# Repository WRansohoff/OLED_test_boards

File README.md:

# Overview

These are KiCAD projects with schematics and footprints for 128x64 SSD1306 monochrome OLED screens and 96x64 SSD1331 multicolor ones. Both panels are roughly 1" diagonally, and the boards are designed for SPI communication.

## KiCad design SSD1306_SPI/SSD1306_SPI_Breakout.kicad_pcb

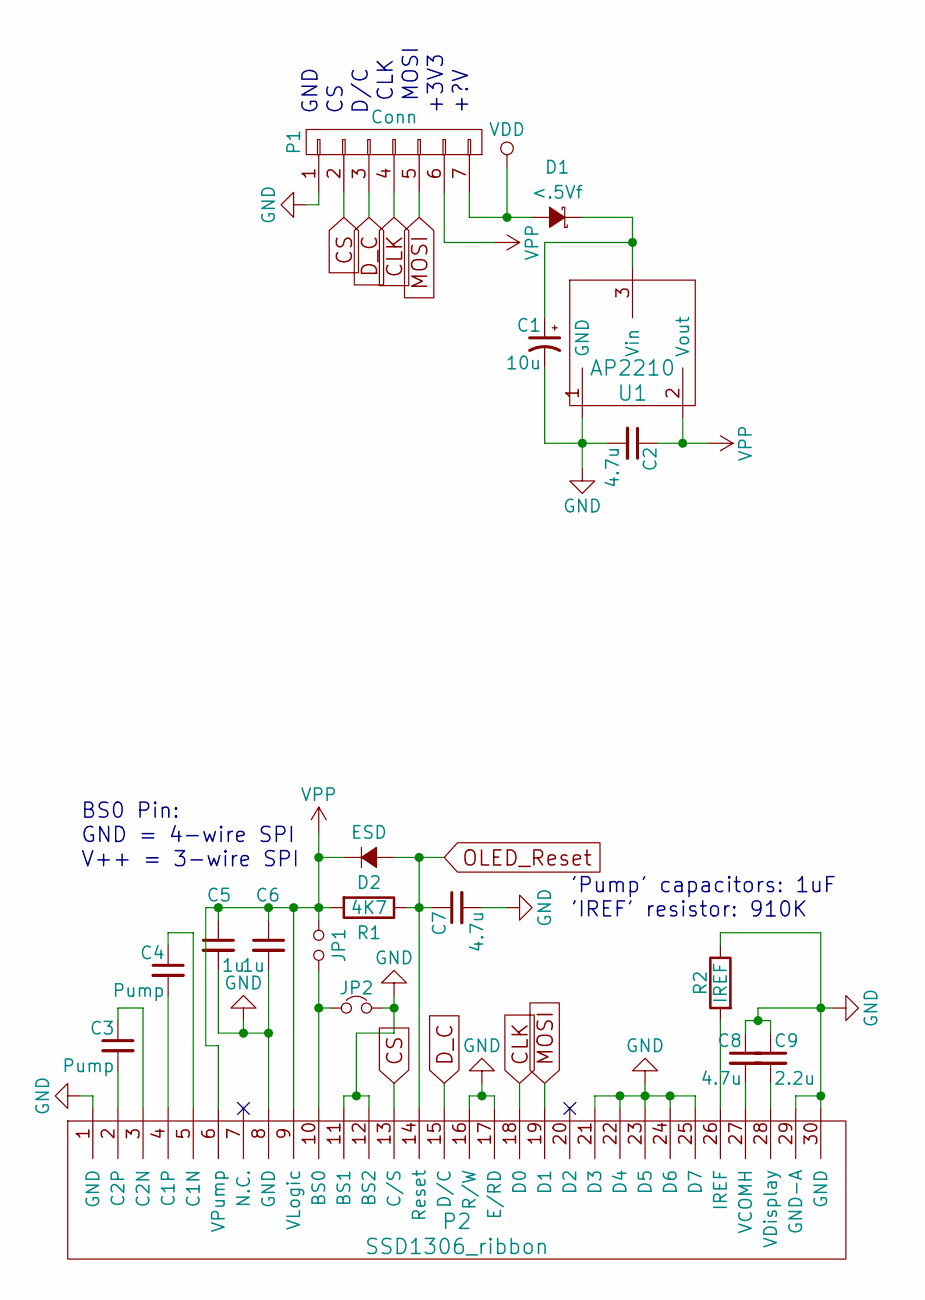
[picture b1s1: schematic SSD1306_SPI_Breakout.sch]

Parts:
C1: 10u; TantalC_SizeA_EIA-3216_HandSoldering
C2, C7, C8: 4.7u; C_0805_HandSoldering
C3, C4: Pump; C_0805_HandSoldering
C5, C6: 1u; C_0805_HandSoldering
C9: 2.2u; C_0805_HandSoldering
D1: <.5Vf; SOD-123
D2: ESD; SOD-123
JP1: Jumper_NO_Small; R_0805_HandSoldering
JP2: Jumper_NC_Small; R_0805_HandSoldering
P1: Conn; Pin_Header_Straight_1x07
P2: SSD1306_ribbon
R1: 4K7; R_0805_HandSoldering
R2: IREF; R_0805_HandSoldering
U1: AP2210; SOT-23_Handsoldering

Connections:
CLK: P1.4, P2.18 (D0)
CS: P1.2, P2.13 (C/S)
D_C: P1.3, P2.15 (D/C)
GND: C1.2, C2.2, C5.2, C6.2, C7.2, C8.1, C9.1, JP2.2, P1.1, P2.1 (GND), P2.8 (GND), P2.11 (BS1), P2.12 (BS2), P2.16 (R/W), P2.17 (E/RD), P2.21 (D3), P2.22 (D4), P2.23 (D5), P2.24 (D6), P2.25 (D7), P2.29 (GND-A), P2.30 (GND), R2.1, U1.1 (GND)
MOSI: P1.5, P2.19 (D1)
unnamed: C1.1, D1.1 (K), U1.3 (Vin)
unnamed: C3.1, P2.3 (C2N)
unnamed: C3.2, P2.2 (C2P)
unnamed: C4.1, P2.5 (C1N)
unnamed: C4.2, P2.4 (C1P)
unnamed: C8.2, P2.27 (VCOMH)
unnamed: C9.2, P2.28 (VDisplay)
unnamed: JP1.1, JP2.1, P2.10 (BS0)
unnamed: P2.26 (IREF), R2.2
OLED_Reset: C7.1, D2.2 (A), P2.14 (Reset), R1.1
VDD: D1.2 (A), P1.7
VPP: C2.1, C5.1, C6.1, D2.1 (K), JP1.2, P1.6, P2.6 (VPump), P2.9 (VLogic), R1.2, U1.2 (Vout)

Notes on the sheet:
BS0 Pin: GND = 4-wire SPI V++ = 3-wire SPI
GND
D/C
CLK
MOSI
+3V3
+?V
'Pump' capacitors: 1uF 'IREF' resistor: 910K

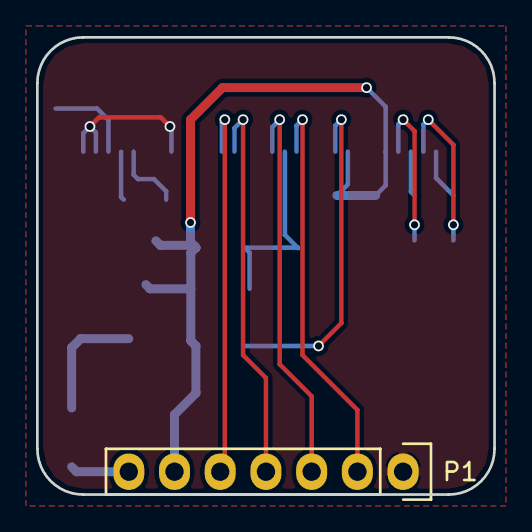
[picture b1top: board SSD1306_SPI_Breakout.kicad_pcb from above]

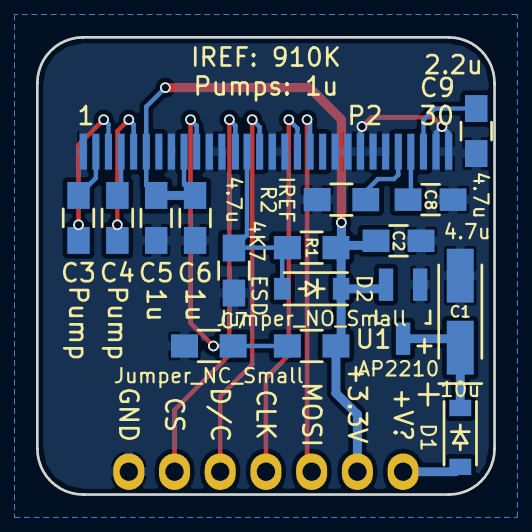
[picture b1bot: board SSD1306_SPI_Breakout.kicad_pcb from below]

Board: 2 copper layers, 25.4 x 25.4 mm, 18 parts (17 on the bottom side), 17 nets.

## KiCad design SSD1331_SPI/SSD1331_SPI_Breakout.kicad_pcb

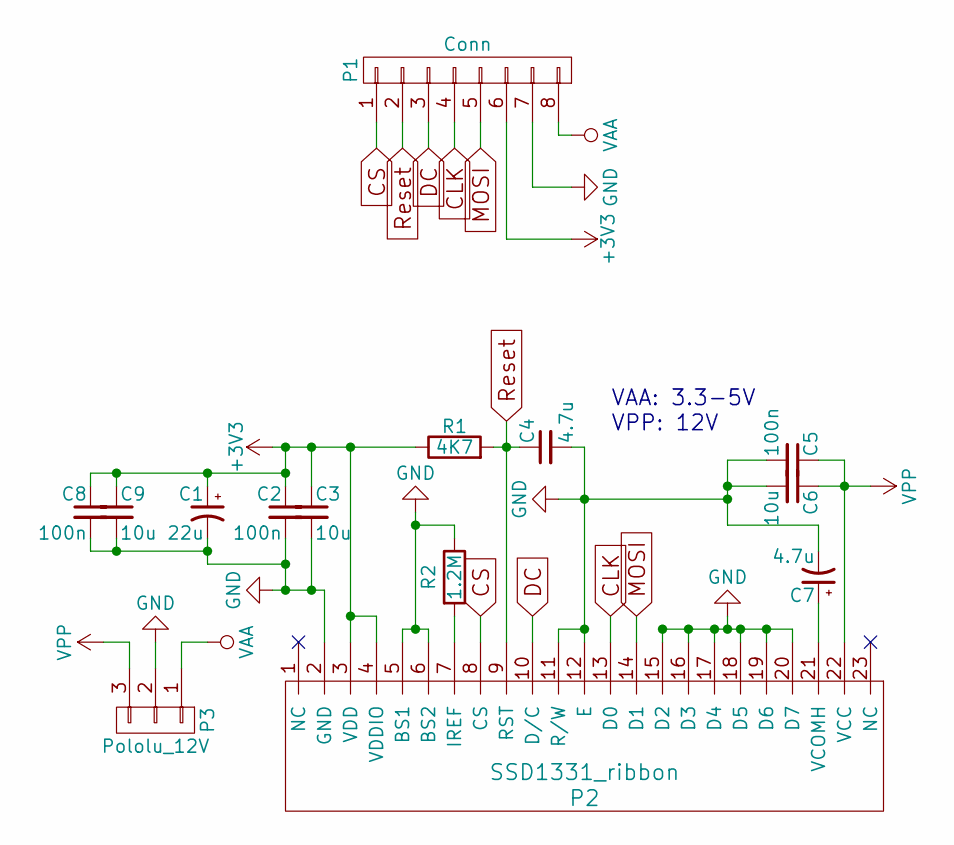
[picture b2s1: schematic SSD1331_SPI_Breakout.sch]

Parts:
C1: 22u; TantalC_SizeA_EIA-3216_HandSoldering
C2, C5, C8: 100n; C_0805_HandSoldering
C3, C6, C9: 10u; C_0805_HandSoldering
C4, C7: 4.7u; C_0805_HandSoldering
P1: Conn; Pin_Header_Angled_1x08
P2: SSD1331_ribbon
P3: Pololu_12V; Pin_Header_Straight_1x03
R1: 4K7; R_0805_HandSoldering
R2: 1.2M; R_0805_HandSoldering

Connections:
+3V3: C1.1, C2.1, C3.1, C8.1, C9.1, P1.6, P2.3 (VDD), P2.4 (VDDIO), R1.1
CLK: P1.4, P2.13 (D0)
CS: P1.1, P2.8 (CS)
DC: P1.3, P2.10 (D/C)
GND: C1.2, C2.2, C3.2, C4.2, C5.2, C6.2, C7.2, C8.2, C9.2, P1.7, P2.2 (GND), P2.5 (BS1), P2.6 (BS2), P2.11 (R/W), P2.12 (E), P2.15 (D2), P2.16 (D3), P2.17 (D4), P2.18 (D5), P2.19 (D6), P2.20 (D7), P3.2, R2.1
MOSI: P1.5, P2.14 (D1)
unnamed: C7.1, P2.21 (VCOMH)
unnamed: P2.7 (IREF), R2.2
Reset: C4.1, P1.2, P2.9 (RST), R1.2
VAA: P1.8, P3.1
VPP: C5.1, C6.1, P2.22 (VCC), P3.3

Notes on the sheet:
VAA: 3.3-5V VPP: 12V

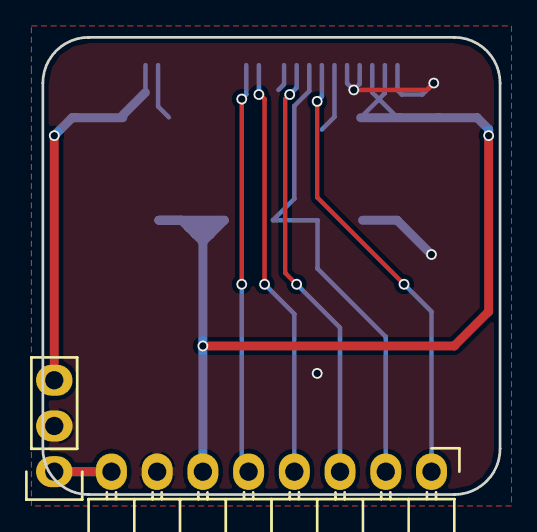
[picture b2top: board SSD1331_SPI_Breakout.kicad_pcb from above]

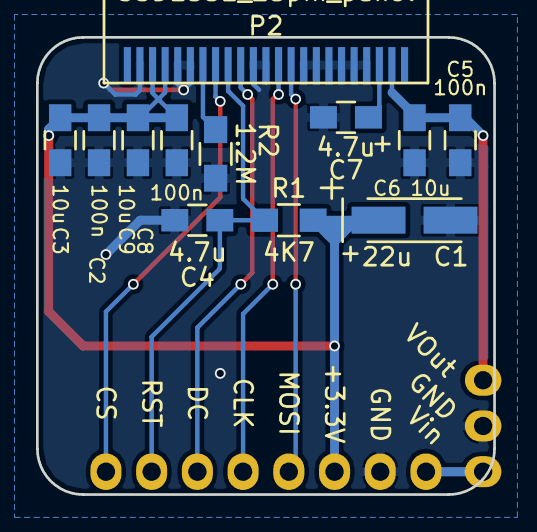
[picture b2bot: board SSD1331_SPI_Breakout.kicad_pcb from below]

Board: 2 copper layers, 25.4 x 25.4 mm, 14 parts (12 on the bottom side), 11 nets.

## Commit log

2018-04-20 Initial commit; I hope these KiCAD projects all work with the relative paths.
2018-04-20 Add a license/readme.
